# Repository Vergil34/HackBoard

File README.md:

# ButtonBox
Hack Club Blueprint Starter Project. This is my first time working in-depth with creating a PCB or CADing something to actually bring it to life, so it was definitely a fun experience. I plan to use this as a small button box for sim racing, but it can probably be easily reprogrammed to be a regular macro pad.

## Features:
- 3D printed case. I did something pretty simple since I'm new to cadding
- 128x32 OLED Display, because why not?
- 2 SK6812 MINI-E LEDs just for some lights
- 4 keys

## CAD
Held together with 4 M3x16mm screws +  4x M3x5mx4mm heatset inserts, the pcb doesnt have too much space to move around, so I didn't mount it with a screw. 2 pieces for the print, top cover, and bottom holder.

Used Fusion 360, hooray for school accounts

## PCB
Used KICAD, and wasnt as complicated as I thought it was gonna be originally.

Schematic:

PCB:

## Firmware

I used KMK for everything. I was originally planning to do QMK, but I felt like it would take too long to get the custom profile approved (Im doing this way too late)

-OLED screen will display date and time, a small clock wouldn't be a bad addition to my setup
-4 Keys that will be bound to a key on my regular keyboard and then be used to turn things like the headlights of a car, or if I want to turn onthe wipers, etc in game. Can be very easily changed by programming. To be finalized when I get the box built. 

##BOM: 
The parts needed:
- 4x Cherry MX-Switches
- 4x DSA Keycaps
- 1x 0.91" 128x32 OLED Display
- 1x XIAO RP2040
- 1x Case (2 printed parts)
- 4x M3x5mx4mm heatset inserts
- 4x M3x16mm screws

##Extra Stuff
I'm not sure where I was supposed to put this, but I do need a soldering kit. Thanks!

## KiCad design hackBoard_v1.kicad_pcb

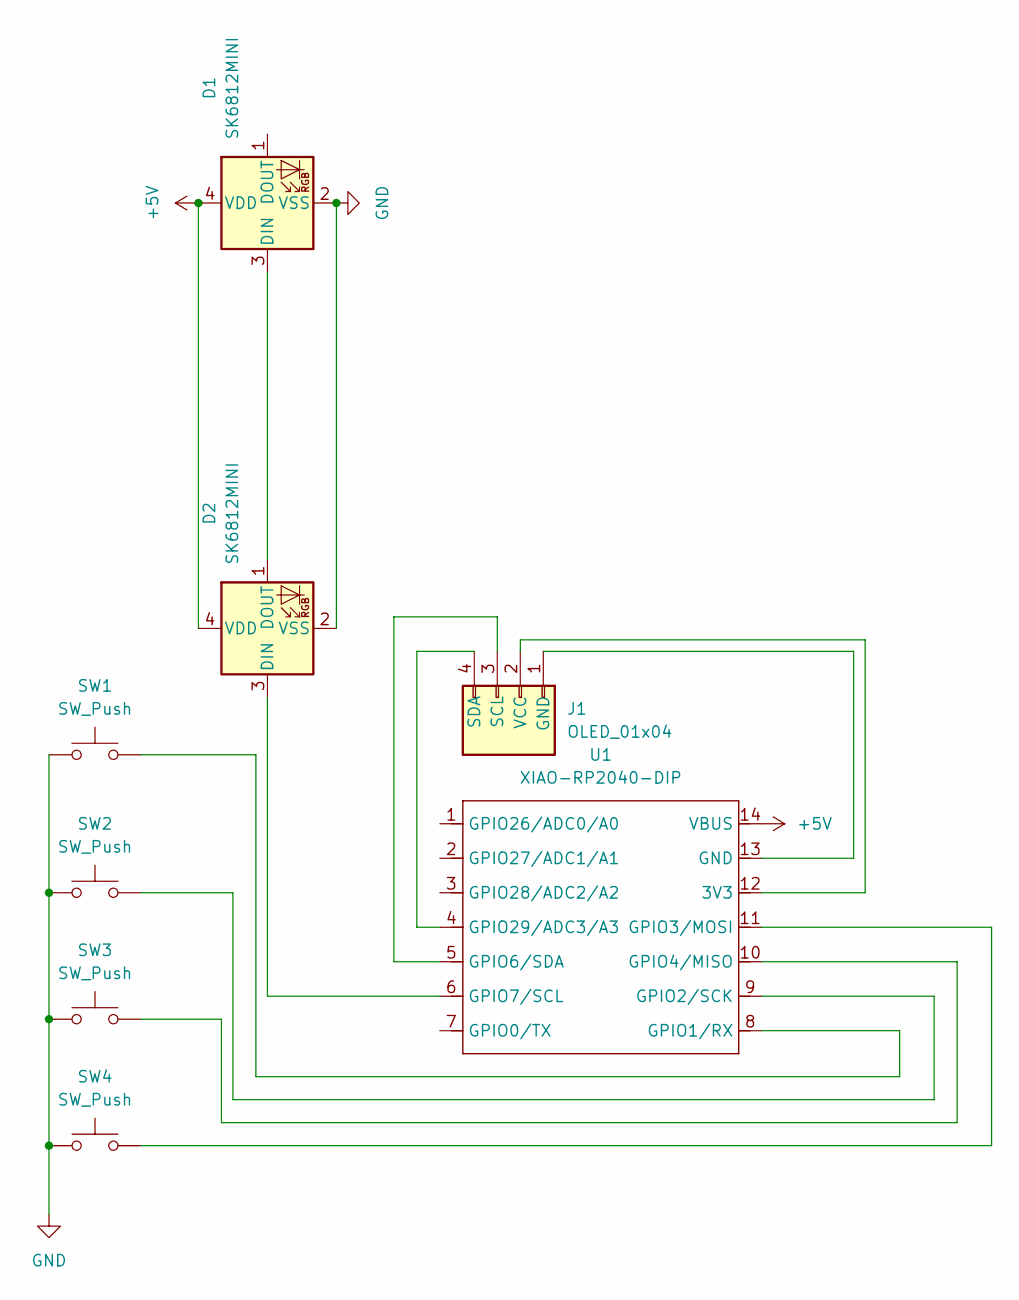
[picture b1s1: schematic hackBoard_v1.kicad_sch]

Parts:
D1, D2: SK6812MINI; LED_SK6812MINI_PLCC4_3.5x3.5mm_P1.75mm
J1: OLED_01x04; Oled Pin header1x4
SW1, SW2, SW3, SW4: SW_Push; SW_Cherry_MX_1.00u_PCB
U1: XIAO-RP2040-DIP

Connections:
+5V: D1.4 (VDD), D2.4 (VDD), U1.14 (VBUS)
GND: D1.2 (VSS), D2.2 (VSS), SW1.1, SW2.1, SW3.1, SW4.1
unnamed: D1.3 (DIN), D2.1 (DOUT)
unnamed: D2.3 (DIN), U1.6 (GPIO7/SCL)
unnamed: J1.1 (GND), U1.13 (GND)
unnamed: J1.3 (SCL), U1.5 (GPIO6/SDA)
unnamed: J1.4 (SDA), U1.4 (GPIO29/ADC3/A3)
unnamed: J1.2 (VCC), U1.12 (3V3)
unnamed: SW1.2, U1.8 (GPIO1/RX)
unnamed: SW2.2, U1.9 (GPIO2/SCK)
unnamed: SW4.2, U1.11 (GPIO3/MOSI)
unnamed: SW3.2, U1.10 (GPIO4/MISO)

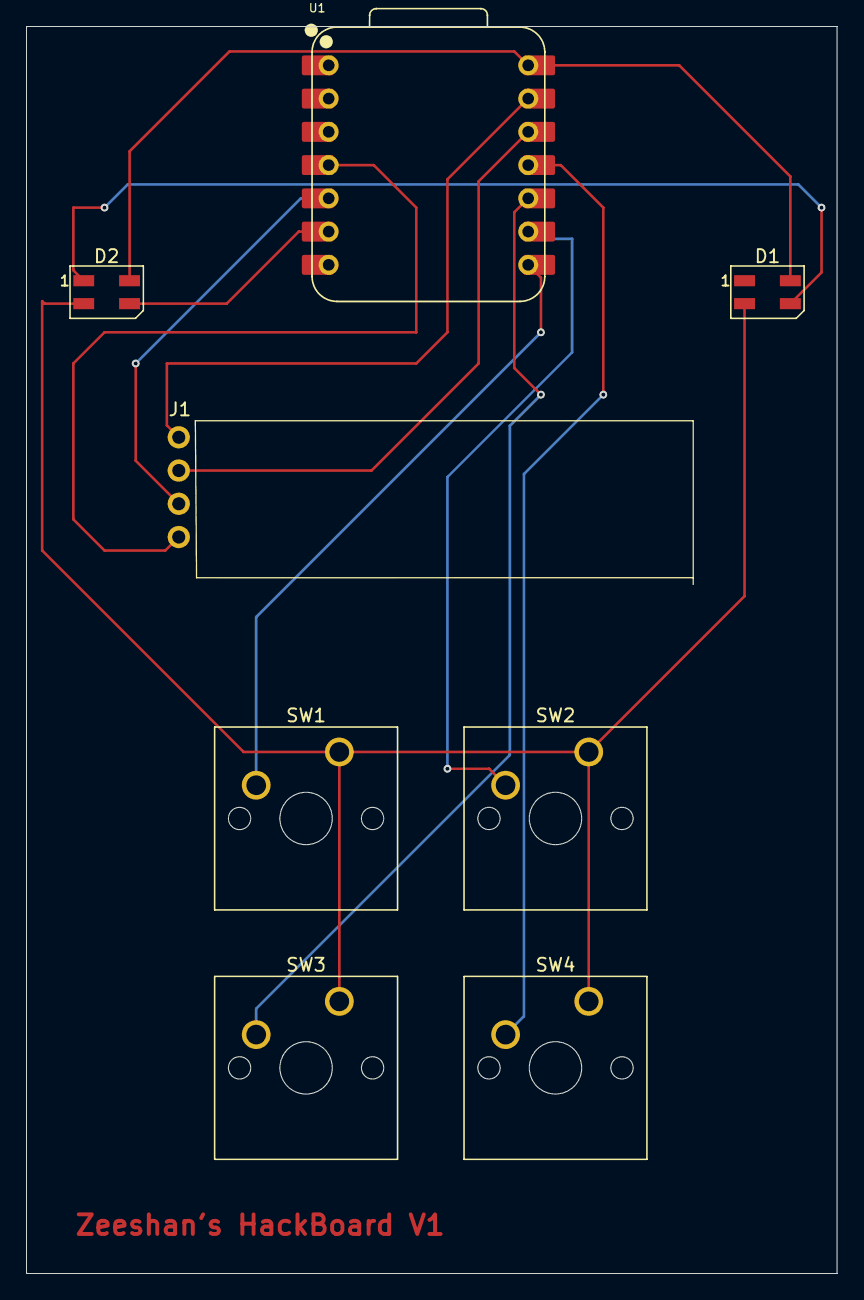
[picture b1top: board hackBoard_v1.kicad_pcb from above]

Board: 2 copper layers, 61.9 x 95.2 mm, 8 parts (0 on the bottom side), 12 nets.

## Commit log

2025-12-26 Added both PCB and CAD files
2025-12-27 Delete hackBoard_v1.kicad_pro
    Had to redo the files to put them in correct folders
2025-12-27 Delete hackBoard_v1.kicad_sch
    Had to redo the files to put them in correct folders
2025-12-27 added Cad File in the right place
2025-12-27 Created 1 as a place holder file for folder
2025-12-27 Delete Firmware/1
    deleted place holder
2025-12-27 Delete Firmware directory
    decided to replace qmk for kmk
